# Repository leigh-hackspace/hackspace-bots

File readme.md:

# Hackspace-Bots

Below is the information for the build of the Hackspace-Bots project

---

## Objective:

The Hackspace-Bots project aims to create a Small 3 wheeled robot that is capable of being controlled using a bluetooth interface.

---

## Components:

The project requires a combination of hardware and software components

You will need:

[Raspberry Pi Pico W][1]

[Stepper motor controller][2]

[2 x Motors and wheels][3]

[18650 Battery and Charger][4]

[2x 18650 holder][5]

Connector Board and Wires (Schematics for this board will be available once they are finished)

A basic understanding of micro-python.

And perhaps most importantly an imagination

---
During this project we aim to produce a step-by-step guide to building your very own hackspace bot! 

** Join the Hackspace-Bots project and dive into the exciting world of robotics within a collaborative and innovative community! **

First off, you'll need to put micropython on your PicoW you can follow the instructions [here][6].

Once that's done you'll need [Thonny][7] so go ahead and download, then install it.

Running thonny, go to the top and the `Run >  Configure Interpreter` option, in the _port_ option select
`Try to detect automatically` and click OK

We're not ready to select our adventure:

[1]: https://shop.pimoroni.com/products/raspberry-pi-pico-w?variant=40059369619539
[2]: https://components101.com/modules/l293n-motor-driver-module
[3]: https://www.amazon.co.uk/dp/B07VBXXT9M/ref=cm_sw_r_api_i_BB50HXYKHPBAT04PZ3PT_0
[4]: https://www.amazon.co.uk/Flashlight-Universal-Battery-Batteries-Rechargeable/dp/B08P7QHRFL
[5]: https://www.amazon.co.uk/Battery-holder-lithium-connection-battery/dp/B07F2LN6F5
[6]: https://projects.raspberrypi.org/en/projects/get-started-pico-w/1
[7]: https://thonny.org/ 
[8]: [todo]

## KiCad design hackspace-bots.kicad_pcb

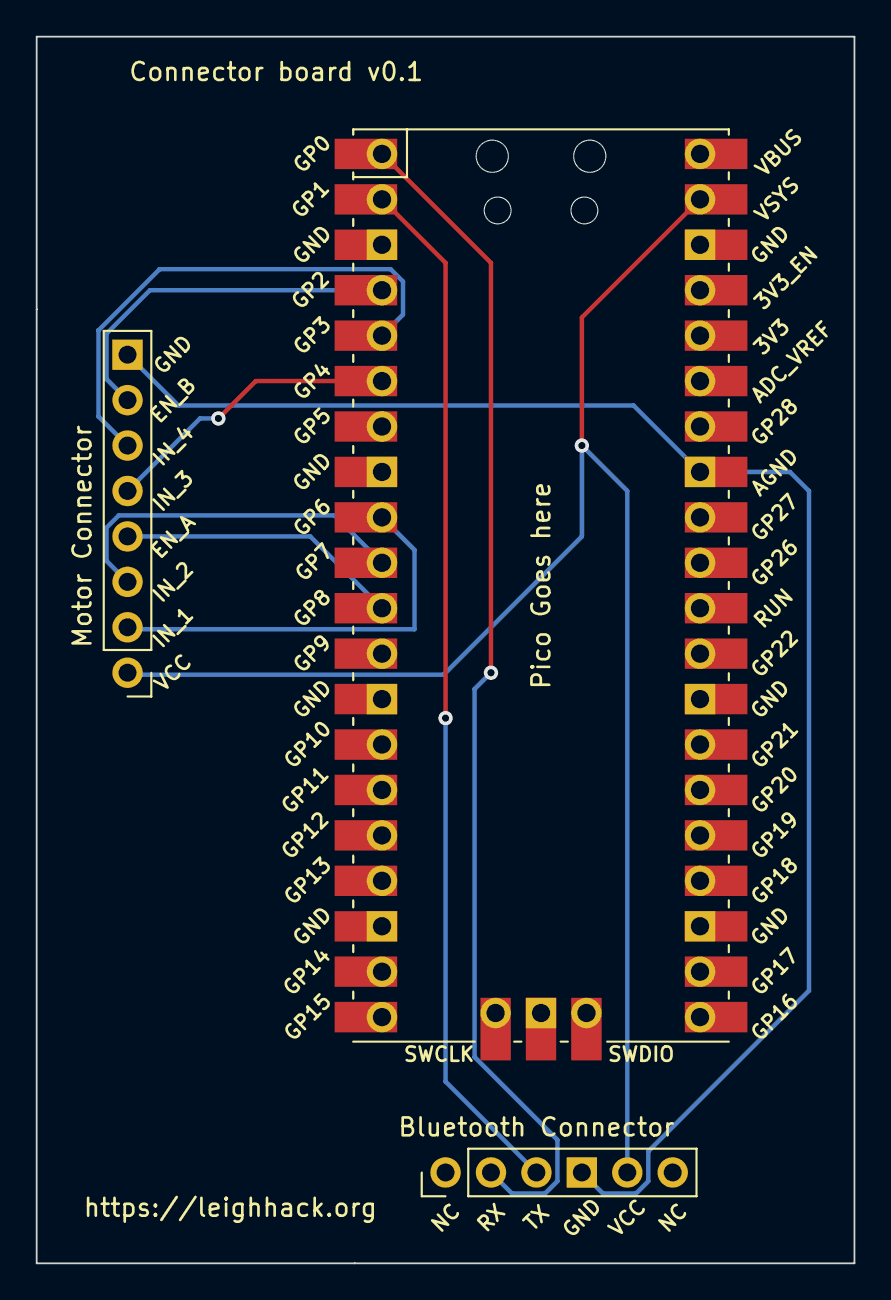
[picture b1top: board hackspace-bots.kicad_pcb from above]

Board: 2 copper layers, 45.7 x 68.6 mm, 3 parts (0 on the bottom side), 11 nets.

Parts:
Bluetooth Connector: Bluetooth connector; PinHeader_1x06_P2.54mm_Vertical
Motor Connector: L298-N Motor-driver; PinHeader_1x08_P2.54mm_Vertical
Pico Goes here: Pico; RPi_Pico_SMD_TH

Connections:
EN_A: Motor Connector.4, Pico Goes here.11 (GPIO8)
EN_B: Motor Connector.7, Pico Goes here.4 (GPIO2)
GND: Bluetooth Connector.4, Motor Connector.8, Pico Goes here.33 (AGND)
IN_1: Motor Connector.2, Pico Goes here.9 (GPIO6)
IN_2: Motor Connector.3, Pico Goes here.10 (GPIO7)
IN_3: Motor Connector.5, Pico Goes here.6 (GPIO4)
IN_4: Motor Connector.6, Pico Goes here.5 (GPIO3)
NC: Bluetooth Connector.1, Bluetooth Connector.6
RX: Bluetooth Connector.2, Pico Goes here.1 (GPIO0)
TX: Bluetooth Connector.3, Pico Goes here.2 (GPIO1)
VCC: Bluetooth Connector.5, Motor Connector.1, Pico Goes here.39 (VSYS)

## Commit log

2023-05-07 Add inital kicad files
2023-05-07 move into folder
2023-05-07 Inital commit
2023-05-07 add readme
2023-05-08 Add indicator that the Pico receives power
2023-05-31 Rework controller to use a web app on the pico w
2023-05-31 Rework controller to use a web app on the pico w (#3)
2023-09-09 Push code that was demo'd at the park event
2023-11-04 Move the HTML to it's own page
2023-11-04 Move The Stylesheet to it's own file, css didn't quite work but i hacked around it
2023-11-04 Change the stylesheet to use css variables to allow easily changing the colours
2023-11-29 Modify Readme to add Thonny and Micro-python instructions
